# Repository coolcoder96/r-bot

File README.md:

# r-bot
The little companion that does some cool things.

This project is a WORK IN PROGRESS! I'm still updating code and case designs.

# The Reason I buit this
I wanted to make some sort of device that would help me to keep myself on top of my busy life.
I wanted it to be able to remind me of things on my calender and to-do list.
I also wanted to put in a few games when I need a break (instead of scrolling lol), this includes using the presence sensor to get me to get up and move around my room.

# Parts
The r-bot is made up of:
| Part     | Link    |
| -------- | ------- |
| Seedstudio Xiao ESP32S3  |  https://www.aliexpress.com/item/1005005637495945.html   |
| HLK-LD2450 |https://www.aliexpress.com/item/4000049991220.html    |
| 1.5 Inch 128x128 OLED    |  https://www.aliexpress.com/item/4000049991220.html   |
| 5 WS2812B Leds | https://www.aliexpress.com/item/4001345875756.html |
| ENS160+AHT21 Air Quality And Temperature And Humidity Sensor |  https://www.aliexpress.com/item/1005005637495945.html |

Thanks for taking a look!
# Other Pics

Original plan:

Upcoming case:

PCB and Schematic pics:
(Autotracer really saved me with this one)

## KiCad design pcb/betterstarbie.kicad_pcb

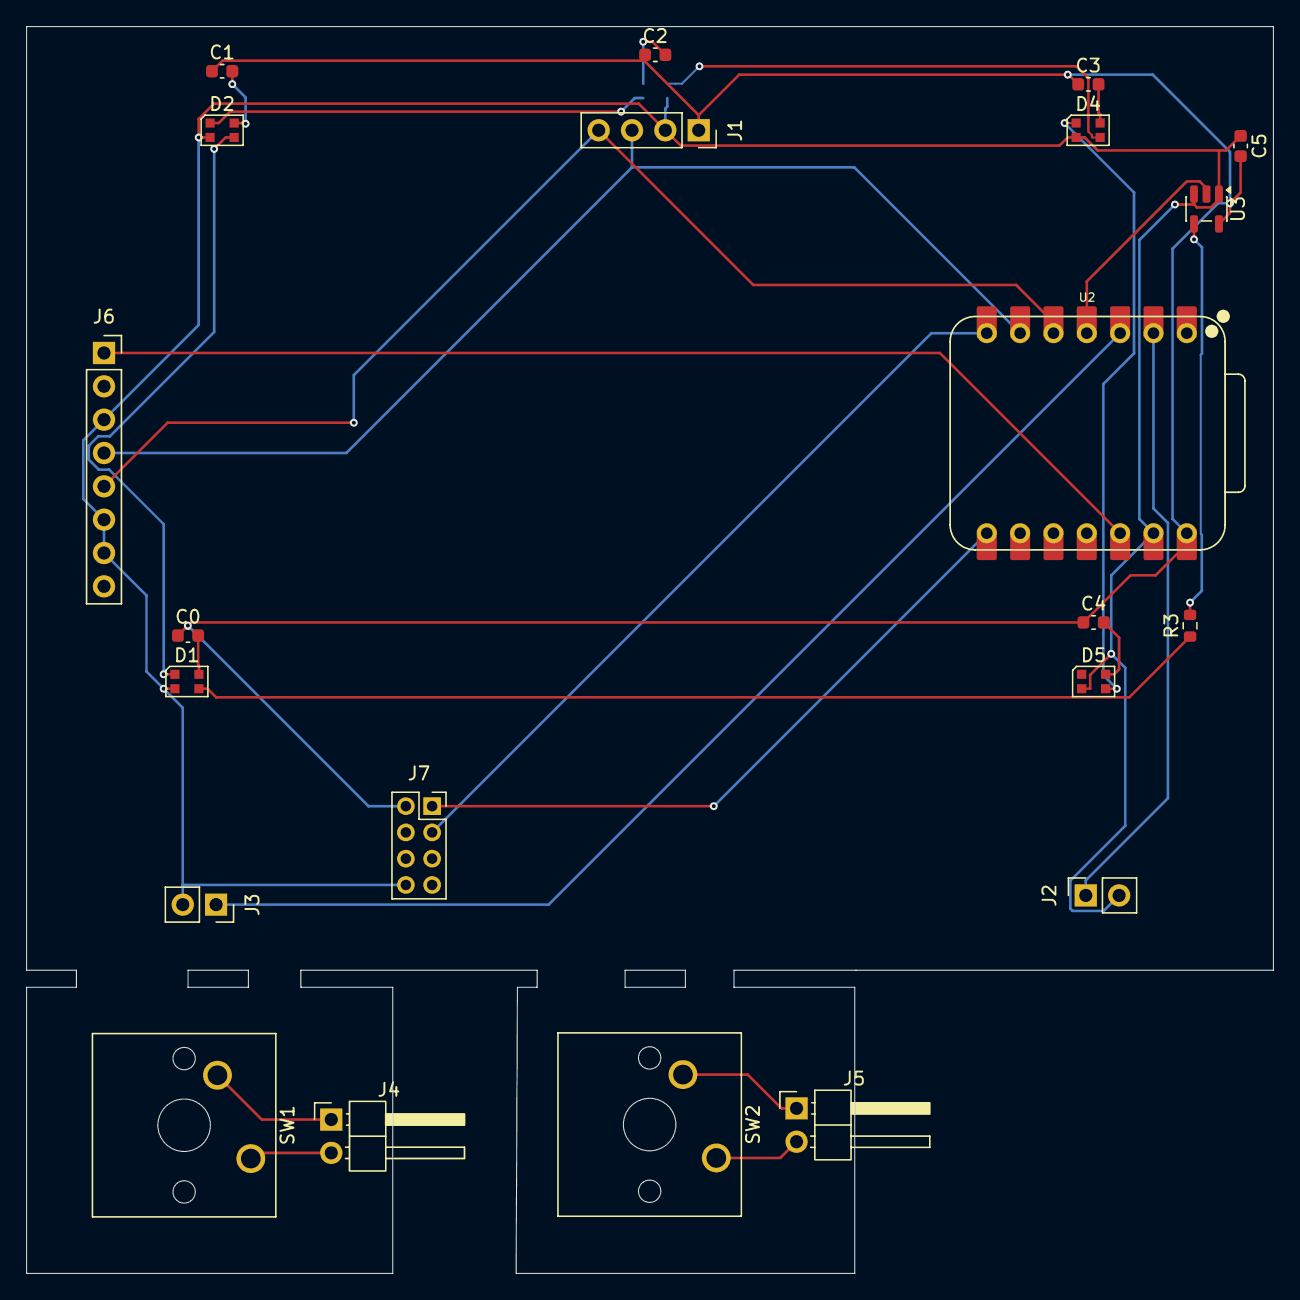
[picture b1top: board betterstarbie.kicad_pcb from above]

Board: 2 copper layers, 95.0 x 95.0 mm, 23 parts (1 on the bottom side), 25 nets.

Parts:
C0, C1, C2, C3, C4, C5: 100nF; C_0603_1608Metric
D1, D2, D3, D4, D5: WS2812B-2020; LED_WS2812B-2020_PLCC4_2.0x2.0mm
J1: OLED_SH1107_1.5in; PinSocket_1x04_P2.54mm_Vertical
J2, J3: Conn_01x02_Socket; PinSocket_1x02_P2.54mm_Vertical
J4, J5: Conn_01x02_Pin; PinHeader_1x02_P2.54mm_Horizontal
J6: ENS160+AHT21; PinSocket_1x08_P2.54mm_Vertical
J7: HLK-LD2450 2x4 2.00mm; PinSocket_2x04_P2.00mm_Vertical
R3: 330Ω; R_0603_1608Metric
SW1, SW2: SW_Push; SW_Cherry_MX_1.00u_PCB
U2: XIAO-ESP32-S3-SMD; XIAO-ESP32-S3-DIP
U3: 74AHCT1G125; SOT-23-5

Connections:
+3.3V: J6.1, U2.12 (3V3_OUT)
+5V: C0.1, C1.1, C2.1, C3.1, C4.1, C5.2, J1.1, J7.2, U2.14 (VBUS), U3.5 (VCC)
/BTN1: J2.1, U2.2 (D1)
/BTN2: J3.1, U2.3 (D2)
/LED Data: U2.4 (D3), U3.2
/RADAR_RX: J7.1, U2.8 (D7)
/RADAR_TX: J7.3, U2.7 (D6)
/SCL: J1.3, J6.4, U2.6 (D5)
/SDA: J1.4, J6.5, U2.5 (D4)
GND: C5.1, D1.2 (VSS), D2.2 (VSS), D3.2 (VSS), D4.2 (VSS), D5.2 (VSS), J1.2, J2.2, J3.2, J6.3, J6.6, J6.7, J7.8, U2.13 (GND), U3.1, U3.3 (GND)
unnamed: D1.3 (DIN), R3.1
unnamed: D1.1 (DOUT), D2.3 (DIN)
unnamed: C0.2, D1.4 (VDD)
unnamed: D2.1 (DOUT), D3.3 (DIN)
unnamed: C1.2, D2.4 (VDD)
unnamed: D3.1 (DOUT), D4.3 (DIN)
unnamed: C2.2, D3.4 (VDD)
unnamed: D4.1 (DOUT), D5.3 (DIN)
unnamed: C3.2, D4.4 (VDD)
unnamed: C4.2, D5.4 (VDD)
unnamed: J4.1, SW1.2
unnamed: J4.2, SW1.1
unnamed: J5.1, SW2.2
unnamed: J5.2, SW2.1
unnamed: R3.2, U3.4
